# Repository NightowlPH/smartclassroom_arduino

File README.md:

# SmartClassroom_Arduino

Arduino code for the smart classroom project and the schematics for the circuit boards.

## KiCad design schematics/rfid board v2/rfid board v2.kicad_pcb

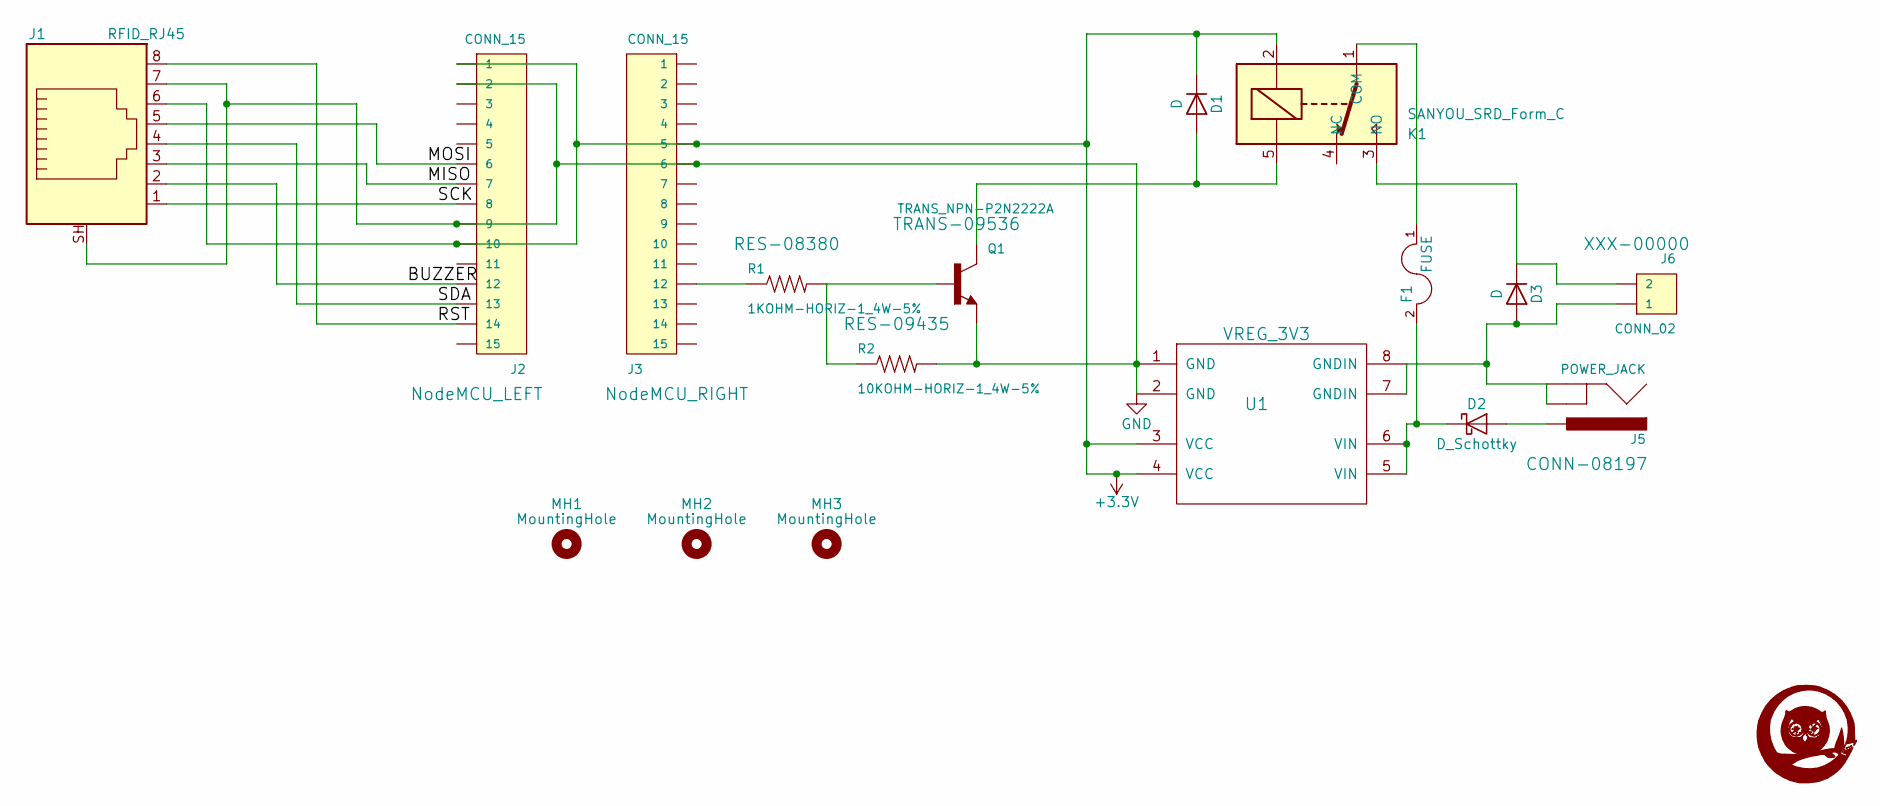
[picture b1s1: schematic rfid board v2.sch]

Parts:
D1, D3: D; Diode_DO-41_SOD81_Horizontal_RM10
D2: D_Schottky; Diode_DO-41_SOD81_Horizontal_RM10
F1: FUSE; Fuseholder5x20_horiz_SemiClosed_Casing10x25mm
J1: RFID_RJ45; MAGJACK2
J2, J3: CONN_15; 1X15
J5: POWER_JACK; POWER_JACK_PTH
J6: CONN_02; SCREWTERMINAL-5MM-2
K1: SANYOU_SRD_Form_C; Relay_SPDT_SANYOU_SRD_Series_Form_C
MH1, MH2, MH3: MountingHole; MountingHole_3mm
Q1: TRANS_NPN-P2N2222A; TO-92-AMMO
R1: 1KOHM-HORIZ-1_4W-5%; AXIAL-0.3
R2: 10KOHM-HORIZ-1_4W-5%; AXIAL-0.3
U1: VREG_3V3

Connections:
+3V3: D1.1 (K), J1.6, J2.1, J2.10, J3.5, K1.2, U1.3 (VCC), U1.4 (VCC)
/BUZZER: J1.2, J2.12
/MISO: J1.3, J2.7
/MOSI: J1.5, J2.6
/RST: J1.8, J2.14
/SCK: J1.1, J2.8
/SDA: J1.4, J2.13
GND: J1.7, J1.SH, J2.2, J2.9, J3.6, Q1.1 (E), R2.P$2 (2), U1.1 (GND), U1.2 (GND)
unnamed: D1.2 (A), K1.5, Q1.3 (C)
unnamed: D2.1 (K), F1.2, U1.5 (VIN), U1.6 (VIN)
unnamed: D2.2 (A), J5.PWR
unnamed: D3.1 (K), J6.2, K1.3 (NO)
unnamed: D3.2 (A), J5.GND, J5.GNDB (GNDBREAK), J6.1, U1.7 (GNDIN), U1.8 (GNDIN)
unnamed: F1.1, K1.1 (COM)
unnamed: J3.12, R1.P$1 (1)
unnamed: Q1.2 (B), R1.P$2 (2), R2.P$1 (1)

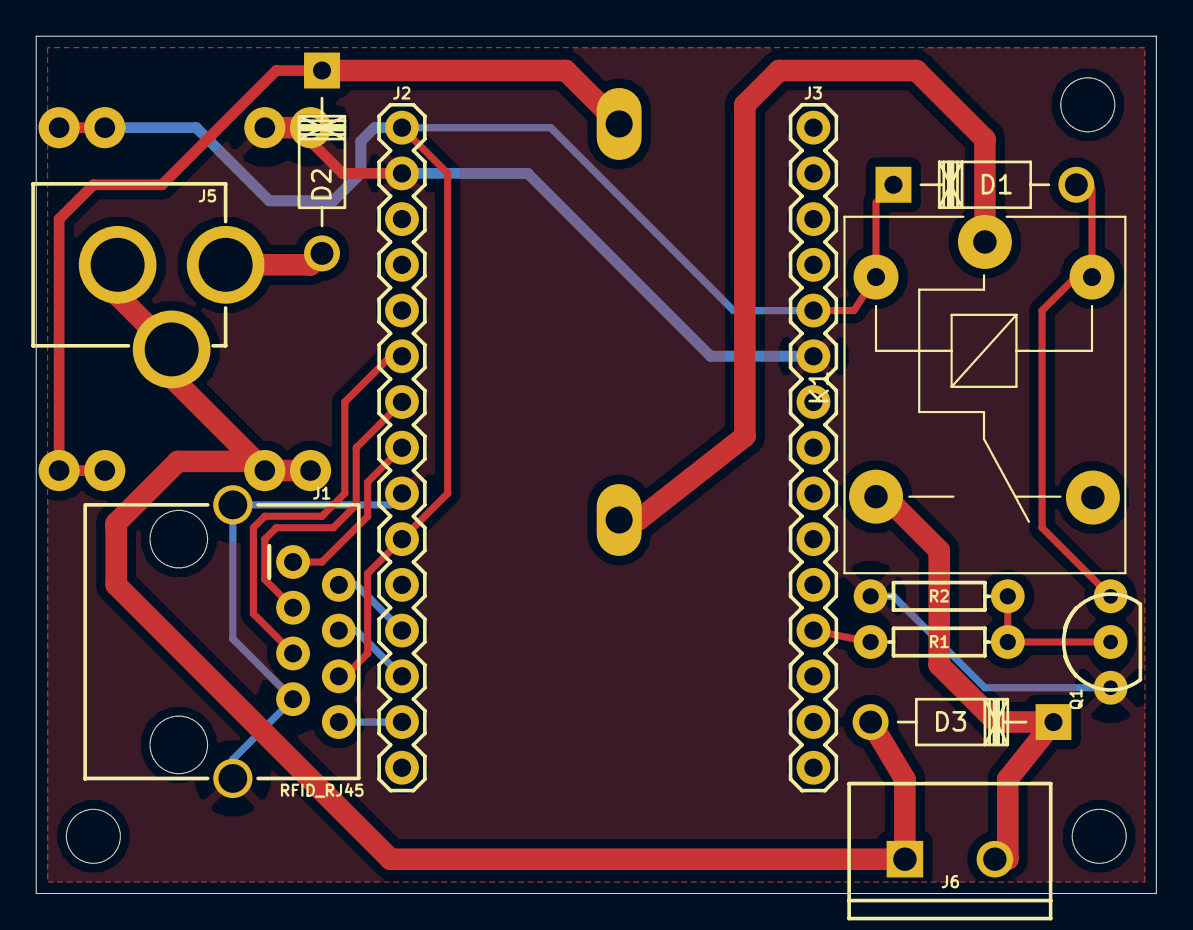
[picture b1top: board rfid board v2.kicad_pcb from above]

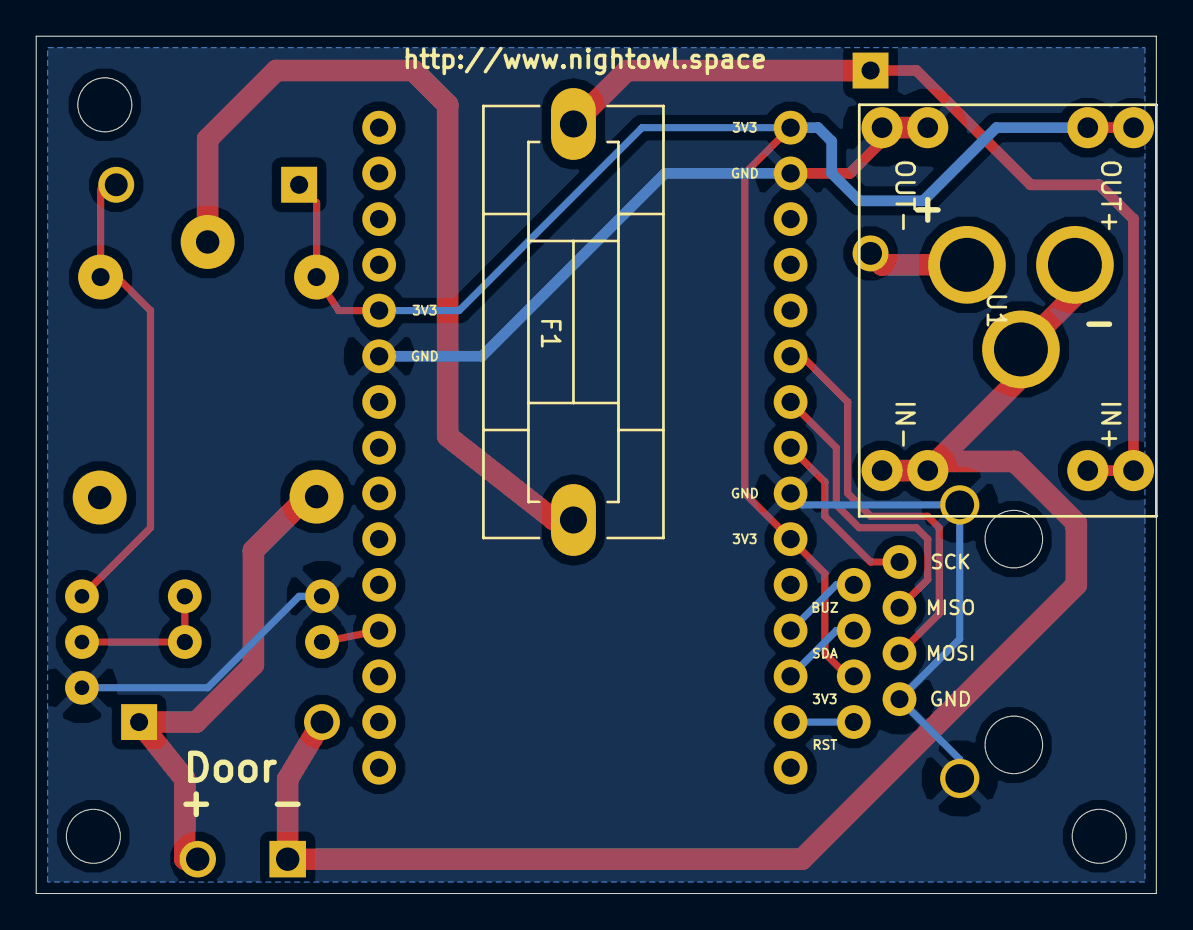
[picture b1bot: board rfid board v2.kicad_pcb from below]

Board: 2 copper layers, 62.2 x 47.6 mm, 17 parts (2 on the bottom side), 16 nets.

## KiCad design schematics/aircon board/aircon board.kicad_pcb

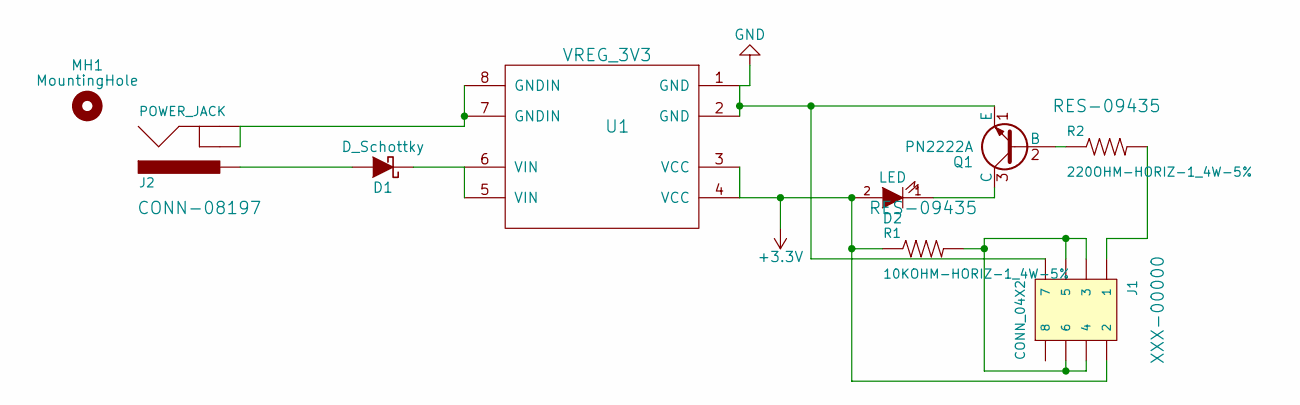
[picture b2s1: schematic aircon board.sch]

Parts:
D1: D_Schottky; Diode_DO-41_SOD81_Horizontal_RM10
D2: LED; LED-5MM
J1: CONN_04X2; 2X4
J2: POWER_JACK; POWER_JACK_PTH
MH1: MountingHole; MountingHole_3mm
Q1: PN2222A; TO-92-AMMO
R1: 10KOHM-HORIZ-1_4W-5%; AXIAL-0.3
R2: 220OHM-HORIZ-1_4W-5%; AXIAL-0.3
U1: VREG_3V3

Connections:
+3V3: D2.2 (A), J1.2, R1.P$1 (1), U1.3 (VCC), U1.4 (VCC)
GND: J1.7, Q1.1 (E), U1.1 (GND), U1.2 (GND)
unnamed: D1.1 (K), U1.5 (VIN), U1.6 (VIN)
unnamed: D1.2 (A), J2.PWR
unnamed: D2.1 (K), Q1.3 (C)
unnamed: J1.1, R2.P$2 (2)
unnamed: J1.3, J1.4, J1.5, J1.6, R1.P$2 (2)
unnamed: J2.GND, J2.GNDB (GNDBREAK), U1.7 (GNDIN), U1.8 (GNDIN)
unnamed: Q1.2 (B), R2.P$1 (1)

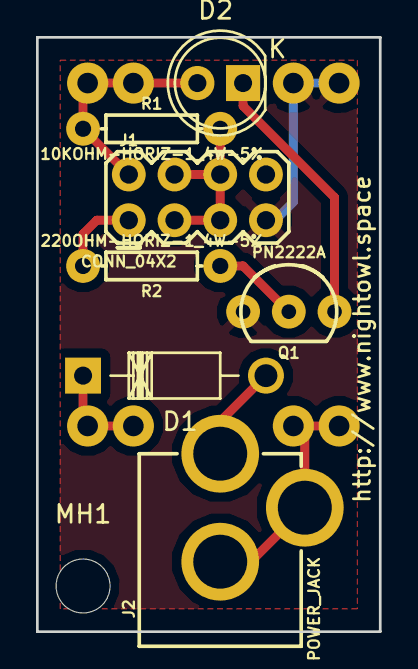
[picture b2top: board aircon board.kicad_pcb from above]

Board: 2 copper layers, 19.1 x 33.0 mm, 9 parts (1 on the bottom side), 9 nets.

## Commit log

2018-01-06 Added rfid code
2018-01-09 esp code with OTA
2018-01-09 Changed settings for node-red
2018-02-12 Change door config plus add aircon control
2018-02-12 change mqtt id
2018-02-15 smart classroom project code for lights
2018-02-19 create folder for esp lights code
2018-02-19 adding IRrecvDumpV2
2018-02-19 Adding code to turn on/off the led once the signal received is matched
2018-02-19 fix encoding
2018-02-19 encoding
2018-02-19 esp826601_lights_mqtt.ino
2018-02-22 Tweaked receiver timing to reduce noise
2018-04-12 Removed configuration values with placeholders
2018-04-12 Removed unused stuff
2018-04-19 Added schematics
2018-04-19 Updated aircon board and added png files
2018-07-18 Added my components and an update to the rfid board
2018-07-19 adding lights_controller_pcb
2018-07-20 modifying lights_controller_pcb into copper fill
2018-07-20 adding img and svg files
2018-07-25 replace old
2018-08-08 Added IR send and receive demos
2018-08-17 modified pcb designs
2018-08-17 replace diode with a schotty diode
2018-08-18 replace lights_controller_pcb2 images with the new updates
2018-08-18 position terminal block to its proper position, update images
2018-08-18 Corrected diodes, terminal blocks and thicker AC traces
2018-08-20 Updated schematics and boards to final version
2018-09-05 Added kicad schematics
2018-09-12 Made vreg 3.3V component pads a little larger
2018-10-31 added pacbiz schematic
2018-10-31 Added svg version of schematic
2018-10-31 added svg files for the rest
2018-12-03 add button switch code, topics to pub and subs sample
2018-12-06 fix button switch code
2018-12-07 remove node_lock() func and replace with lock func in line 156
2019-01-23 updated mqtt topics
2019-01-23 Updated the code for esp-01 to latest
2019-01-24 Brought the mqtt ready for production
2019-01-24 updated code for aircon control, fix
2019-01-25 updated lights stuff
2019-01-28 Adjusted for Daikin Aircon at Dorm
2019-01-28 Add blink function upon mqtt message and startup
2019-01-28 Finished aircon code for production
2019-01-29 Added blink function
2019-02-02 Changed button to different pins and use interrupts and timers instead of delays and check functions. Also use blinking for diagnostics.
2019-02-02 Increase variable sizes for blinking
2019-02-02 Prevent integer overflows
2019-02-09 Changed blinking to use Ticker
2019-02-13 Code ready for production for both the lab and dorm
2019-03-15 Made separate smart classroom libary and refactored the aircon code to match it
2019-03-15 Changed file names
2019-03-15 Add build folder
2019-03-15 rmeove temp files
2019-03-15 Add build directories and sample settings
2019-03-15 Added esp01 preferences and renamed a variable in aircon code
2019-03-16 Reworked aircon and lights code to include local building and smart_classroom library
2019-03-16 Modified door code to work with smart_classroom library
2019-03-18 Refactor subscribing to topics and report version when connecting
2019-04-03 Changed door button interrupt pin detection to HIGH instead of RISING
2019-04-03 Updated components to match new libaries
